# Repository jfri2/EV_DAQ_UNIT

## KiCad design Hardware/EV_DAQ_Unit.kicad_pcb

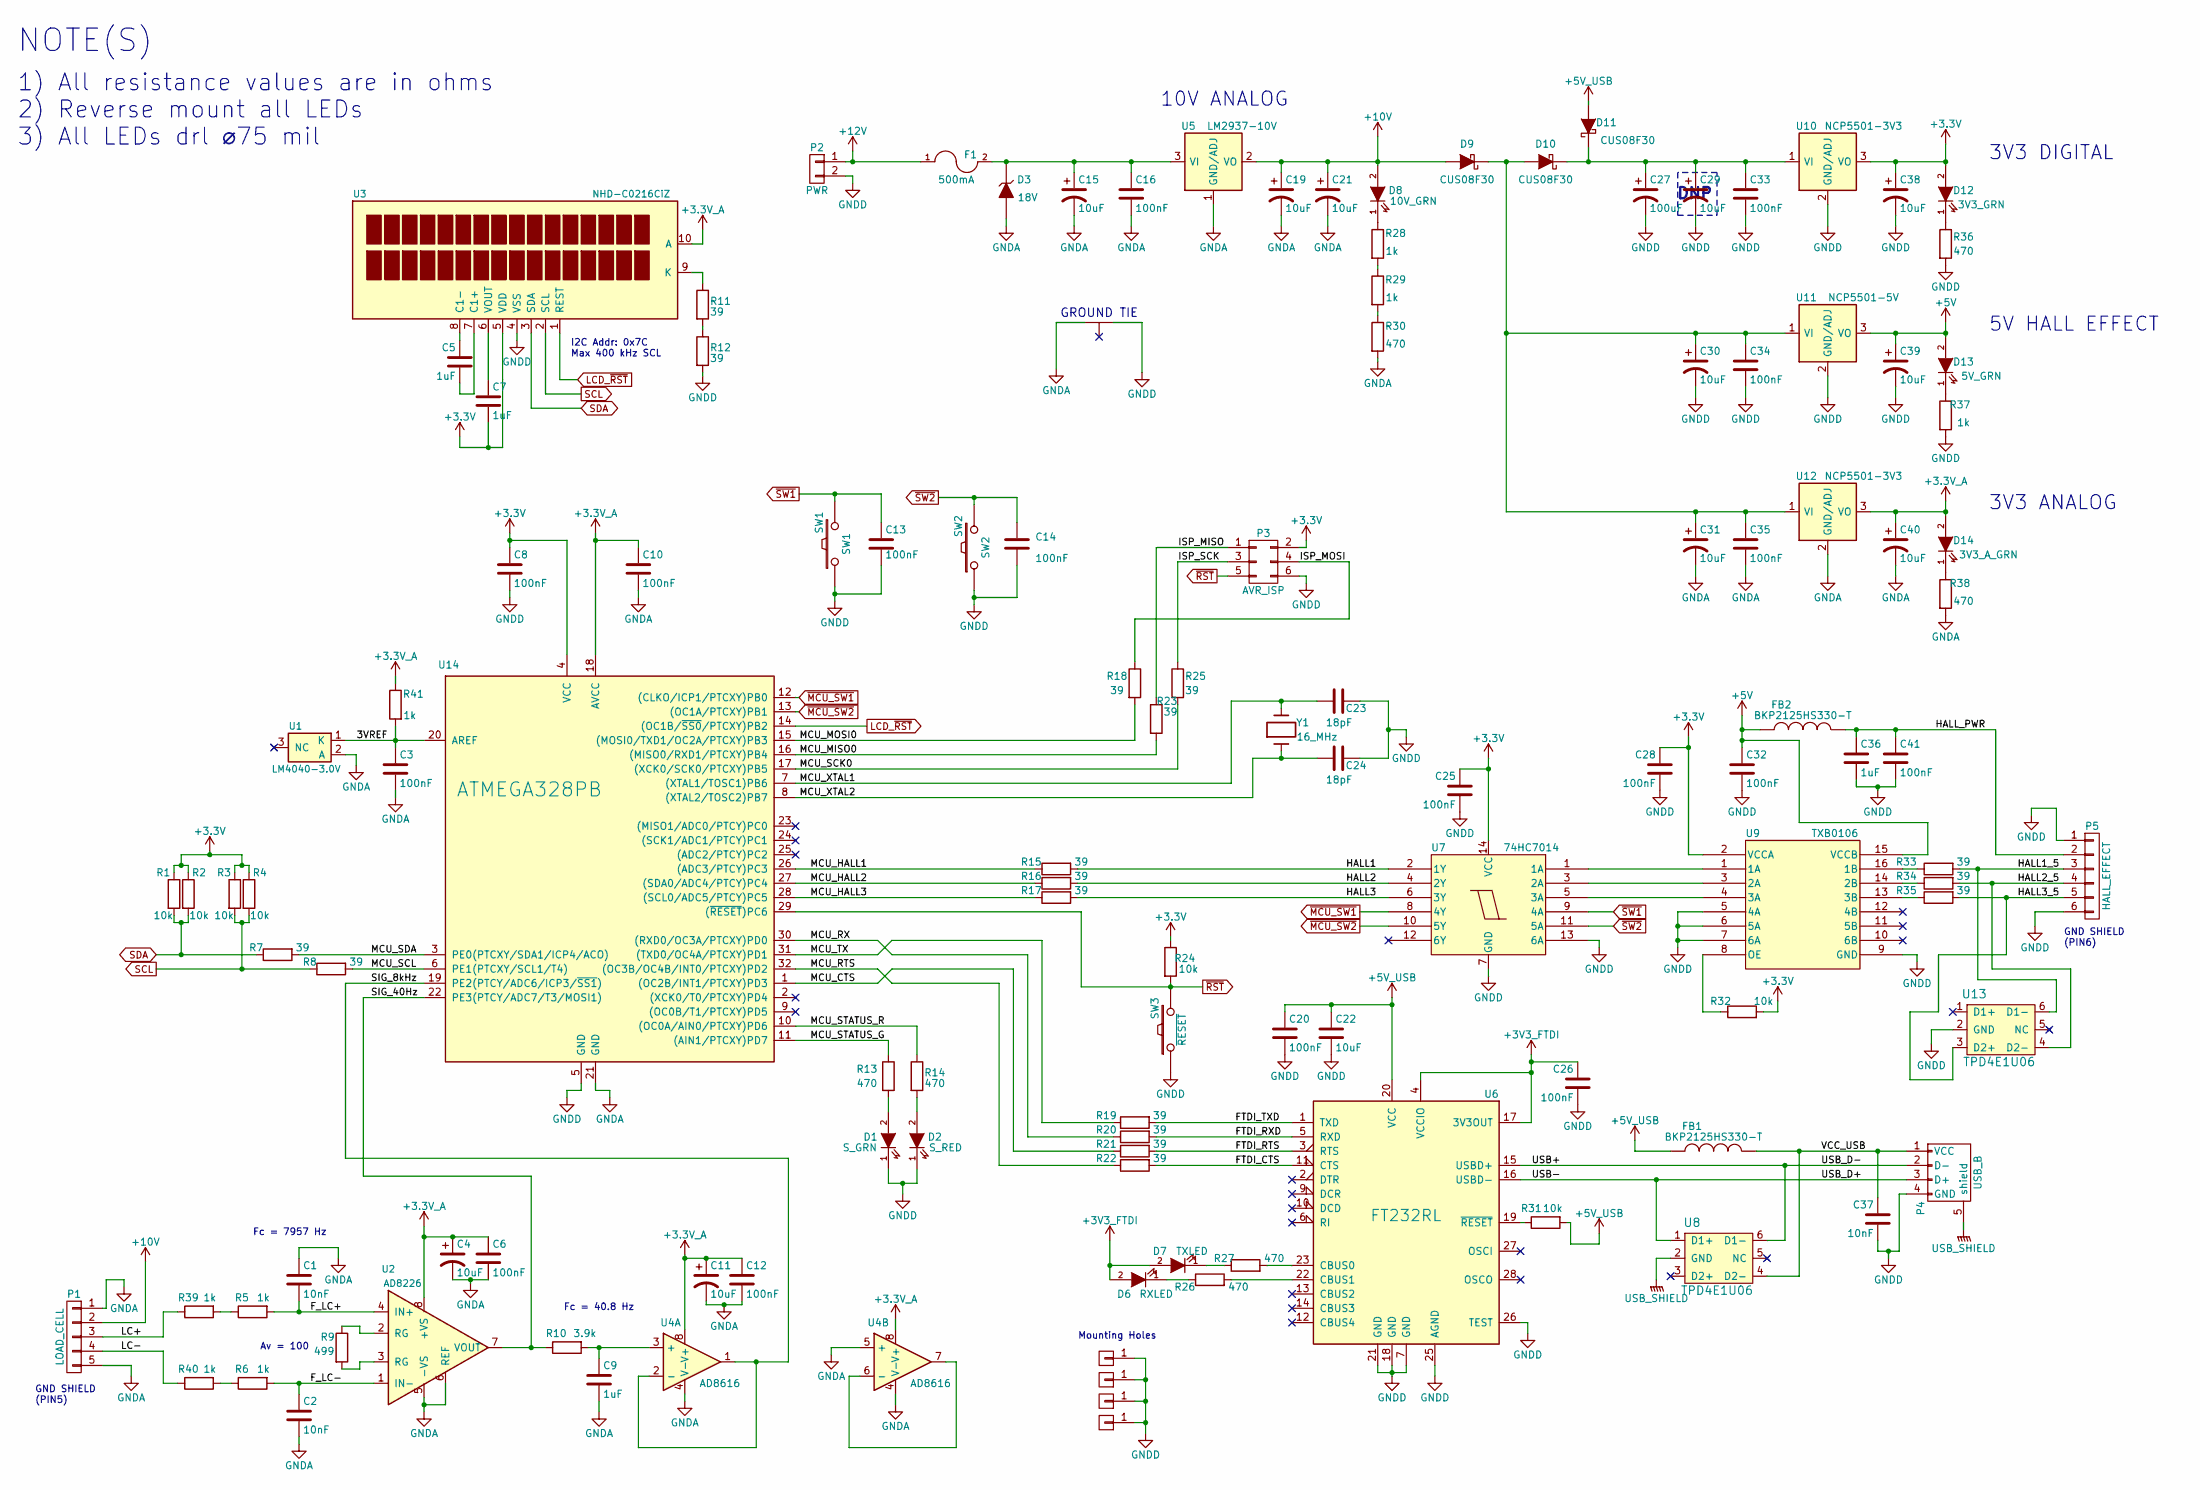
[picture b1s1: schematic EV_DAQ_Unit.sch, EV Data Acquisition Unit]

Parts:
C1, C2, C37: 10nF; C_0805_HandSoldering
C3, C6, C8, C10, C12, C13, C14, C16, C20, C25, C26, C28, C32, C33, C34, C35, C41: 100nF; C_0603_HandSoldering
C4, C11, C15, C19, C21, C22, C29, C30, C31, C38, C39, C40: 10uF; C_1210_HandSoldering_Polarized
C5, C7, C9, C36: 1uF; C_0805_HandSoldering
C23, C24: 18pF; C_0603_HandSoldering
C27: 100uF; TantalC_SizeD_EIA-7343_HandSoldering; MFG# T495D107M016ATE125
D1: S_GRN; 2-SMD_Z-Bend; MFG# SSL-LXA228GC-TR31
D2: S_RED; 2-SMD_Z-Bend; MFG# SSL-LXA228IC-TR31
D3: 18V; SMA_Handsoldering
D6: RXLED; 2-SMD_Z-Bend; MFG# SSL-LXA228YC-TR31
D7: TXLED; 2-SMD_Z-Bend; MFG# SSL-LXA228YC-TR31
D8: 10V_GRN; 2-SMD_Z-Bend; MFG# SSL-LXA228GC-TR31
D9, D10, D11: CUS08F30; SOD-323
D12: 3V3_GRN; 2-SMD_Z-Bend; MFG# SSL-LXA228GC-TR31
D13: 5V_GRN; 2-SMD_Z-Bend; MFG# SSL-LXA228GC-TR31
D14: 3V3_A_GRN; 2-SMD_Z-Bend; MFG# SSL-LXA228GC-TR31
F1: 500mA; R_1812_HandSoldering; MFG# 0ZCG0050AF2C
FB1, FB2: BKP2125HS330-T; R_0805_HandSoldering
GT1: GND_TIE; NetTie-II_Connected_SMD
P1: LOAD_CELL; 1x05_ScrewTerm
P2: PWR; 2x01_ScrewTerm
P3: AVR_ISP; Pin_Header_Straight_2x03
P4: USB_B
P5: HALL_EFFECT; 1x06_ScrewTerm
P7, P8, P9, P10: CONN_01X01; MountingHole_3.2mm_M3_Pad_Via
R1, R2, R3, R4, R24, R31, R32: 10k; R_0603_HandSoldering
R5, R6, R28, R29, R37, R39, R40, R41: 1k; R_0603_HandSoldering
R7, R8, R11, R12, R15, R16, R17, R18, R19, R20, R21, R22, R23, R25, R33, R34, R35: 39; R_0603_HandSoldering
R9: 499; R_0603_HandSoldering
R10: 3.9k; R_0603_HandSoldering
R13, R14, R26, R27, R30, R36, R38: 470; R_0805_HandSoldering
SW1: SW1; SW_TH_Tactile_Omron_B3F-10xx
SW2: SW2; SW_TH_Tactile_Omron_B3F-10xx
SW3: ~RESET; SW_TH_Tactile_Omron_B3F-10xx
U1: LM4040-3.0V; SOT-23
U2: AD8226; SOIC-8_3.9x4.9mm_Pitch1.27mm
U3: NHD-C0216CiZ; NHD-C0216CIZ
U4: AD8616; SOIC-8_3.9x4.9mm_Pitch1.27mm
U5: LM2937-10V; SOT-223
U6: FT232RL; SSOP-28_5.3x10.2mm_Pitch0.65mm
U7: 74HC7014; SOIC-14_3.9x8.7mm_Pitch1.27mm
U8, U13: TPD4E1U06; SOT-23-6
U9: TXB0106; TSSOP-16_4.4x5mm_Pitch0.65mm
U10, U12: NCP5501-3V3; SOT-428_ThermalVias
U11: NCP5501-5V; SOT-428_ThermalVias
U14: ATMEGA328PB; TQFP-32_7x7mm_Pitch0.8mm
Y1: 16_MHz; Q_49U3HMS

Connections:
+3.3V_A: C4.1, C6.1, C10.1, C11.1, C12.1, C40.1, D14.2 (A), R41.1, U2.8 (+VS), U3.10 (A), U4.8 (V+), U12.3 (VO), U14.18 (AVCC)
+3V3: C7.2, C8.1, C25.1, C28.1, C38.1, D12.2 (A), P3.2, R1.1, R2.1, R3.1, R4.1, R24.1, R32.2, U3.5 (VDD), U7.14 (VCC), U9.2 (VCCA), U10.3 (VO), U14.4 (VCC)
+3V3_FTDI: C26.1, D6.2 (A), D7.2 (A), U6.4 (VCCIO), U6.17 (3V3OUT)
+5V: C32.1, C39.1, D13.2 (A), FB2.2, U9.15 (VCCB), U11.3 (VO)
+5V_USB: C20.1, C22.1, D11.2 (A), FB1.2, R31.2, U6.20 (VCC)
+10V: C19.1, C21.1, D8.2 (A), D9.2 (A), P1.2, U5.2 (VO), U5.4 (VO)
+12V: F1.1, P2.1
/3VREF: C3.1, R41.2, U1.1 (K), U14.20 (AREF)
/FTDI_CTS: R22.2, U6.11 (CTS)
/FTDI_RTS: R21.2, U6.3 (RTS)
/FTDI_RXD: R20.2, U6.5 (RXD)
/FTDI_TXD: R19.2, U6.1 (TXD)
/F_LC+: C1.2, R5.2, U2.4 (IN+)
/F_LC-: C2.1, R6.2, U2.1 (IN-)
/HALL1: R15.2, U7.2 (1Y)
/HALL1_5: P5.3, R33.2, U13.6 (D1-)
/HALL2: R16.2, U7.4 (2Y)
/HALL2_5: P5.4, R34.2, U13.4 (D2-)
/HALL3: R17.2, U7.6 (3Y)
/HALL3_5: P5.5, R35.2, U13.3 (D2+)
/HALL_PWR: C36.1, C41.1, FB2.1, P5.2
/ISP_MISO: P3.1, R23.1
/ISP_MOSI: P3.4, R18.1
/ISP_SCK: P3.3, R25.1
/LC+: P1.3, R39.1
/LC-: P1.4, R40.1
/MCU_CTS: R21.1, U14.1 ((OC2B/INT1/PTCXY)PD3)
/MCU_HALL1: R15.1, U14.26 ((ADC3/PTCY)PC3)
/MCU_HALL2: R16.1, U14.27 ((SDA0/ADC4/PTCY)PC4)
/MCU_HALL3: R17.1, U14.28 ((SCL0/ADC5/PTCY)PC5)
/MCU_MISO0: R23.2, U14.16 ((MISO0/RXD1/PTCXY)PB4)
/MCU_MOSI0: R18.2, U14.15 ((MOSI0/TXD1/OC2A/PTCXY)PB3)
/MCU_RTS: R22.1, U14.32 ((OC3B/OC4B/INT0/PTCXY)PD2)
/MCU_RX: R20.1, U14.30 ((RXD0/OC3A/PTCXY)PD0)
/MCU_SCK0: R25.2, U14.17 ((XCK0/SCK0/PTCXY)PB5)
/MCU_SCL: R8.2, U14.6 (PE1(PTCXY/SCL1/T4))
/MCU_SDA: R7.2, U14.3 (PE0(PTCXY/SDA1/ICP4/ACO))
/MCU_STATUS_G: R13.1, U14.11 ((AIN1/PTCXY)PD7)
/MCU_STATUS_R: R14.1, U14.10 ((OC0A/AIN0/PTCXY)PD6)
/MCU_TX: R19.1, U14.31 ((TXD0/OC4A/PTCXY)PD1)
/MCU_XTAL1: C23.1, U14.7 ((XTAL1/TOSC1)PB6), Y1.2
/MCU_XTAL2: C24.1, U14.8 ((XTAL2/TOSC2)PB7), Y1.1
/SIG_8kHz: U4.1, U4.2 (-), U14.19 (PE2(PTCY/ADC6/ICP3/~SS1~))
/SIG_40Hz: R10.1, U2.7 (VOUT), U14.22 (PE3(PTCY/ADC7/T3/MOSI1))
/USB+: P4.2 (D-), U6.15 (USBD+), U8.6 (D1-)
/USB-: P4.3 (D+), U6.16 (USBD-), U8.1 (D1+)
/VCC_USB: C37.1, FB1.1, P4.1 (VCC), U8.4 (D2-)
GNDA: C1.1, C2.2, C3.2, C4.2, C6.2, C9.2, C10.2, C11.2, C12.2, C15.2, C16.2, C19.2, C21.2, C31.2, C35.2, C40.2, D3.2 (A), GT1.1, P1.1, P1.5, R30.2, R38.2, U1.2 (A), U2.5 (-VS), U2.6 (REF), U4.4 (V-), U4.5 (+), U5.1 (GND/ADJ), U12.2 (GND/ADJ), U14.21 (GND)
GNDD: C8.2, C13.2, C14.2, C20.2, C22.2, C23.2, C24.2, C25.2, C26.2, C27.2, C28.2, C29.2, C30.2, C32.2, C33.2, C34.2, C36.2, C37.2, C38.2, C39.2, C41.2, D1.1 (K), D2.1 (K), GT1.3, P2.2, P3.6, P4.4 (GND), P5.1, P5.6, P7.1, P8.1, P9.1, P10.1, R12.2, R36.2, R37.2, SW1.1, SW1.2 (1), SW2.1, SW2.2 (1), SW3.1, SW3.2 (1), U3.4 (VSS), U6.7 (GND), U6.18 (GND), U6.21 (GND), U6.25 (AGND), U6.26 (TEST), U7.7 (GND), U7.13 (6A), U9.5 (4A), U9.6 (5A), U9.7 (6A), U9.9 (GND), U10.2 (GND/ADJ), U11.2 (GND/ADJ), U13.2 (GND), U14.5 (GND)
LCD_~RST: U3.1 (REST), U14.14 ((OC1B/~SS0~/PTCXY)PB2)
unnamed: C5.1, U3.8 (C1-)
unnamed: C5.2, U3.7 (C1+)
unnamed: C7.1, U3.6 (VOUT)
unnamed: C9.1, R10.2, U4.3 (+)
unnamed: C15.1, C16.1, D3.1 (K), F1.2, U5.3 (VI)
unnamed: C27.1, C29.1, C33.1, D10.1 (K), D11.1 (K), U10.1 (VI)
unnamed: C30.1, C31.1, C34.1, C35.1, D9.1 (K), D10.2 (A), U11.1 (VI), U12.1 (VI)
unnamed: D1.2 (A), R13.2
unnamed: D2.2 (A), R14.2
unnamed: D6.1 (K), R26.1
unnamed: D7.1 (K), R27.1
unnamed: D8.1 (K), R28.1
unnamed: D12.1 (K), R36.1
unnamed: D13.1 (K), R37.1
unnamed: D14.1 (K), R38.1
unnamed: R9.1, U2.2 (RG)
unnamed: R9.2, U2.3 (RG)
unnamed: R11.1, U3.9 (K)
unnamed: R11.2, R12.1
unnamed: R26.2, U6.22 (CBUS1)
unnamed: R27.2, U6.23 (CBUS0)
unnamed: R28.2, R29.1
unnamed: R29.2, R30.1
unnamed: R31.1, U6.19 (~RESET~)
unnamed: R32.1, U9.8 (OE)
unnamed: R33.1, U9.16 (1B)
unnamed: R34.1, U9.14 (2B)
unnamed: R35.1, U9.13 (3B)
unnamed: R5.1, R39.2
unnamed: R6.1, R40.2
unnamed: U4.6 (-), U4.7
unnamed: U7.1 (1A), U9.1 (1A)
unnamed: U7.3 (2A), U9.3 (2A)
unnamed: U7.5 (3A), U9.4 (3A)
SCL: R3.2, R4.2, R8.1, U3.2 (SCL)
SDA: R1.2, R2.2, R7.1, U3.3 (SDA)
USB_SHIELD: P4.5 (shield), U8.2 (GND)
~MCU_SW1: U7.8 (4Y), U14.12 ((CLKO/ICP1/PTCXY)PB0)
~MCU_SW2: U7.10 (5Y), U14.13 ((OC1A/PTCXY)PB1)
~RST: P3.5, R24.2, SW3.3, SW3.4, U14.29 ((~RESET~)PC6)
~SW1: C13.1, SW1.3, SW1.4, U7.9 (4A)
~SW2: C14.1, SW2.3, SW2.4, U7.11 (5A)

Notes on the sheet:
GROUND TIE
1) All resistance values are in ohms 2) Reverse mount all LEDs 3) All LEDs drl ⌀75 mil
NOTE(S)
Fc = 7957 Hz
Fc = 40.8 Hz
I2C Addr: 0x7C Max 400 kHz SCL
GND SHIELD (PIN5)
GND SHIELD (PIN6)
Av = 100
3V3 DIGITAL
5V HALL EFFECT
3V3 ANALOG
10V ANALOG
Mounting Holes
DNP

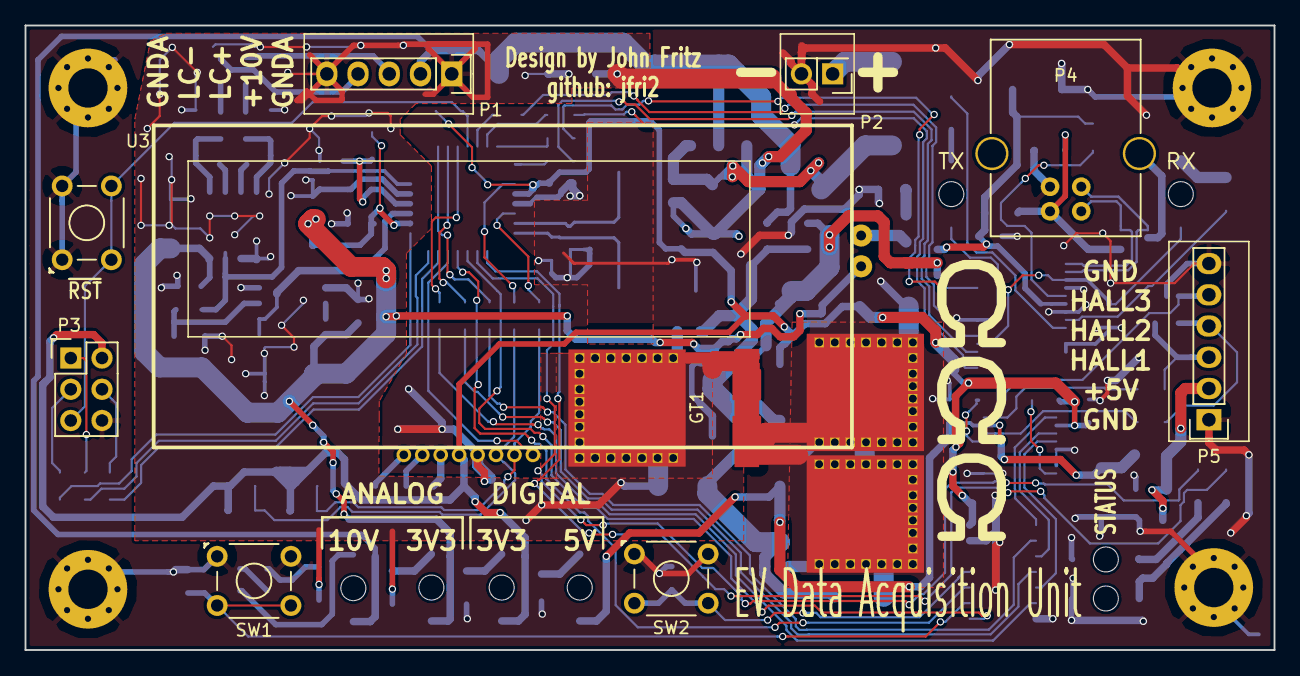
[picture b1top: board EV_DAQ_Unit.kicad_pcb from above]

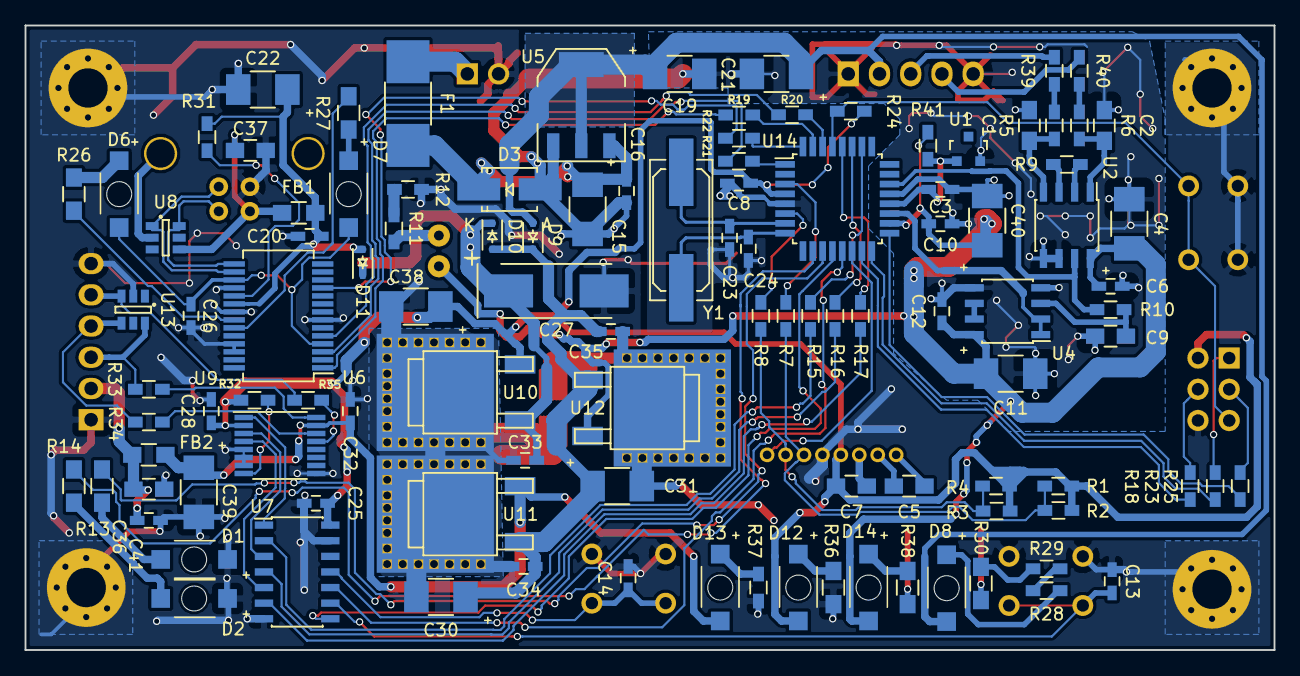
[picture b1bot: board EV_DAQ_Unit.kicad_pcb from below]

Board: 2 copper layers, 101.6 x 50.8 mm, 122 parts (108 on the bottom side), 92 nets.

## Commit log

2016-09-10 :confetti_ball: Added .gitattributes & .gitignore files
2016-09-10 Initial Commit
    Hardware TODO: Regenerate gerbers with current KiCAD board files,
    regenerate PDFs for gerbers and schematic with current KiCAD design
    files.
    Software TODO: Finish driver definitions, Start/Finish library
    definitions, write hardware/software unit tests, start torque sensor
    application code, start speed application code, integration & test of
2016-09-12 I2C driver implemented
    I2C driver implemented (untested) - somethings wrong with the linker
    scripts, at the moment the project will not build
2016-09-12 Refactored some I2C variables&constants
2016-09-12 Added UART/STDIO driver
2016-09-13 Refactored & Fixed linker stuff
2016-09-13 Implemented systck in Timer1, fixed linker stuff again
2016-09-14 Started ADC driver. Implemented & tested 2n averaging function
2016-09-14 Implemented insertion sort for uint16 arrays of size up to 65535
2016-09-15 Finished ADC driver, added more functions to UART driver
2016-09-15 Changed some UART functions and added macros to main
2016-09-15 Refactored a lot of stuff. Started to add things to main
2016-09-15 Updated comments
2016-09-15 Added array copy utility
2016-09-16 Replaced serial.c/h with uart.c/h. Refactor other things
2016-09-16 Added Print module
    This module will contain the STDIO routines for selectable printing over
    the LCD or UART
2016-09-16 Fixed spelling mistake in most c source files
2016-09-16 Changed print functionality to fprintf for both LCD & UART
    fprintf is now used as the default printing function. LCD or UART can be
    selected through the fprintf function call with the macros STDIO_UART or
    STDIO_LCD
2016-09-17 Refactored & Started LCD component defintions
2016-09-17 Refactored sys time implementation, added systck for general timing
    This allows me not to have to use util/delay.h provided that my 64 bit
    integer doesn't overflow (it won't)
2016-09-17 Made systck 32 bits.
2016-09-17 Removed config.h (replaced with EV_DAQ_Unit.h)
2016-09-17 LCD I2C definitions started
2016-09-17 Updated some comments
2016-09-17 Changed some adc & util functions, added basic load cell reading functionality
2016-09-17 Fixed implementation of last commit
2016-09-17 Added TODO
2016-09-17 Updated comments & added TODOs
2016-09-17 Updated TODO again
2016-09-17 Added load cell function declarations & updated doc
2016-09-17 Removed FTDI module
    FTDI module only contained hardware flow control, this can now be
    implemented using the uart module. The UART module will be updated in
    the future
2016-09-17 Removed FTDI module
2016-09-18 Refactored EV_DAQ_Unit.h, moved #defines to specific modules
2016-09-18 Added flow control to UART, refactored stuff
2016-09-20 UART refactored, project rebuilt
2016-09-27 Started LCD test code
2016-09-27 Implemented GPIO & status LED w/ <util/delay.h>
2016-09-27 Fixed systck & implemented custom delay function based on systck
2016-09-27 Updated "blinky" test code
2016-09-27 Removed unused files (now implemented in gpio & EV_DAQ_Unit modules)
2016-09-27 Started working on LCD stuff, changed up GPIO a bit
2016-09-27 Implemented and verified LCD test function
2016-09-28 Altered LCD initialization & general program startup
2016-09-28 Started ADC display. Refactored a ton of stuff
2016-09-29 Implemented and verified ADC
2016-09-29 Rough implementation of Force monitor (Newtons)
    Also verified analog front end performance
2016-09-29 Updated Force LCD print
